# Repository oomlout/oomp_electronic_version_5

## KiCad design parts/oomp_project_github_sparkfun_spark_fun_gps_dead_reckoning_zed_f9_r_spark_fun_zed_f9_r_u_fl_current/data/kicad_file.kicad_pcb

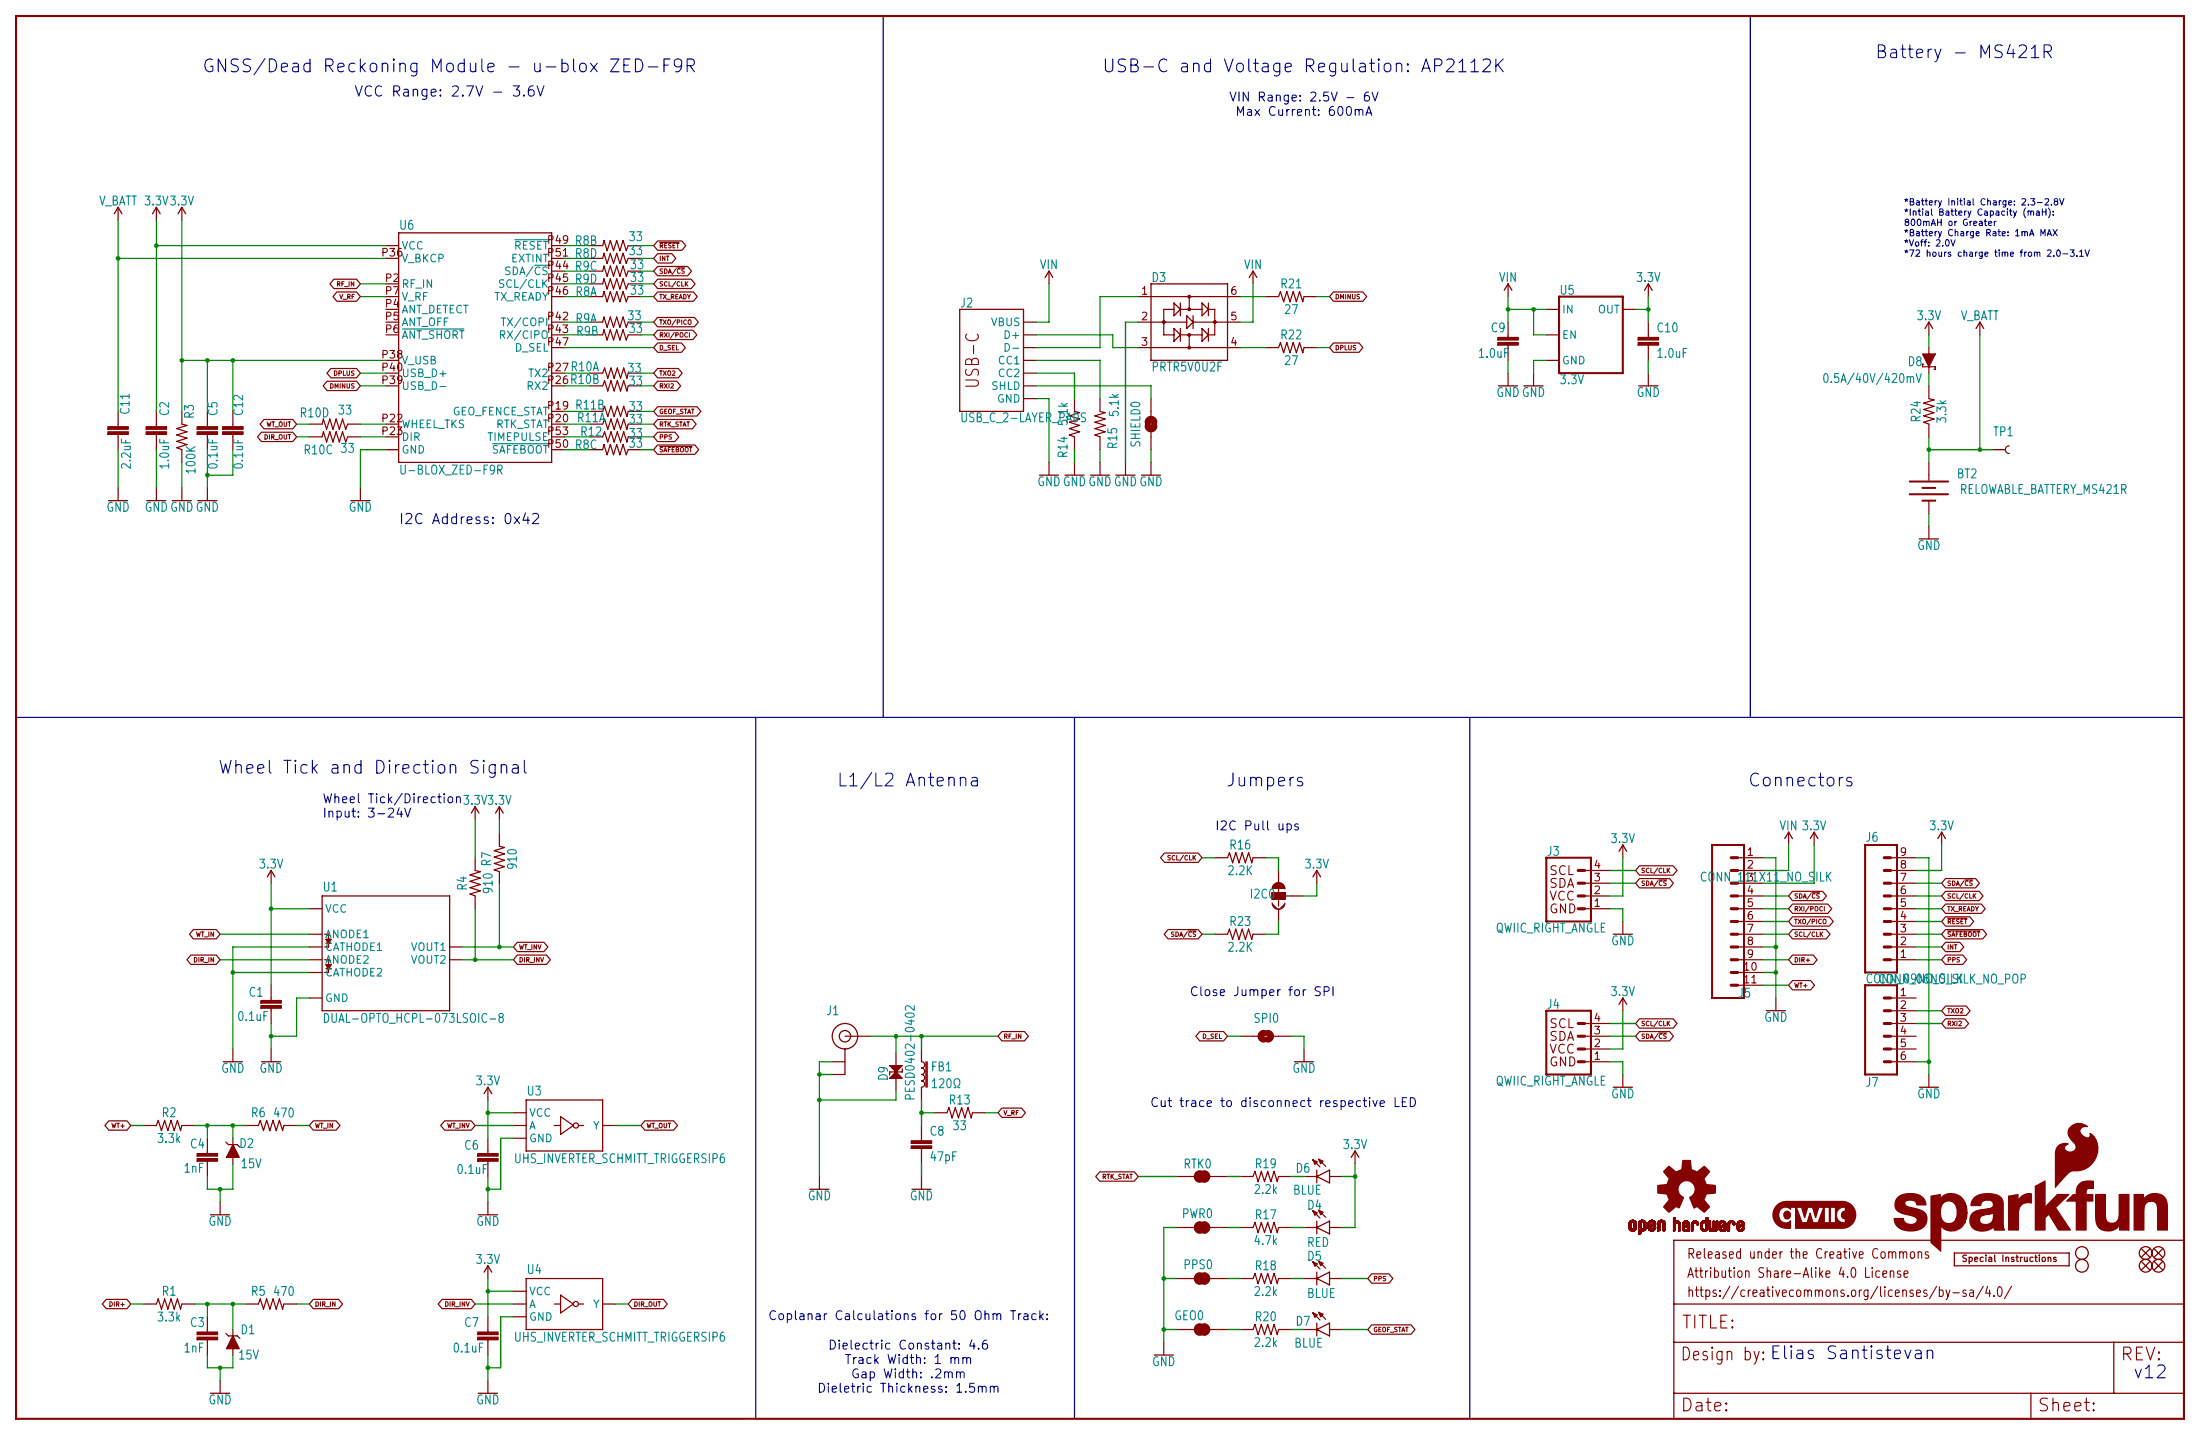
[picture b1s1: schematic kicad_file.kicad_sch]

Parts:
$1_25_$_2020-03-30_22-52-05: STAND-OFFTIGHT; STAND-OFF-TIGHT
BT2: RELOWABLE_BATTERY_MS421R; MS421R_IV03E
C1, C5, C6, C7, C12: 0.1uF; 0402-TIGHT
C2, C9, C10: 1.0uF; 0402-TIGHT
C3, C4: 1nF; 0402
C8: 47pF; 0402
C11: 2.2uF; 0402-TIGHT
D1, D2: 15V; SOT23-3
D3: PRTR5V0U2F; SOT886
D4: RED; LED-0603
D5, D6, D7: BLUE; LED-0603
D8: 0.5A/40V/420mV; SOD-323
D9: PESD0402-0402; 0402; MOUSE_PART 650-PESD0402-140; DIGIKEY_PART PESD0402-140CT-ND
FB1: 120Ω; 0402; MFG_PART BLM15HB121SN1D
FD1, FD2, FD3, FD4: FIDUCIALUFIDUCIAL; FIDUCIAL-MICRO
FRAME1: FRAME-LEDGER; CREATIVE_COMMONS
GEO0: JUMPER-SMT_2_NC_TRACE_SILK; SMT-JUMPER_2_NC_TRACE_SILK
H2: STAND-OFFTIGHT; STAND-OFF-TIGHT
I2C0: JUMPER-SMT_3_2-NC_TRACE_SILK; SMT-JUMPER_3_2-NC_TRACE_SILK
J1: U.FL
J2: USB_C_2-LAYER_PADS; USB-C-16P-2LAYER-PADS
J3, J4: QWIIC_RIGHT_ANGLE; JST04_1MM_RA
J5: CONN_111X11_NO_SILK; 1X11_NO_SILK
J6: CONN_09NO_SILK; 1X09_NO_SILK
J7: CONN_06NO_SILK_NO_POP; 1X06_NO_SILK
LOGO1: OSHW-LOGOS; OSHW-LOGO-S
LOGO2: QWIIC_LOGO_4MM; QWIIC_4MM
LOGO3: SFE_LOGO_NAME_FLAME.2_INCH; SFE_LOGO_NAME_FLAME_.2
LOGO5: SPECIAL_INSTRUCTIONS-ORDERING; ORDERING_INSTRUCTIONS
PPS0: JUMPER-SMT_2_NC_TRACE_SILK; SMT-JUMPER_2_NC_TRACE_SILK
PWR0: JUMPER-SMT_2_NC_TRACE_SILK; SMT-JUMPER_2_NC_TRACE_SILK
R1, R2, R24: 3.3k; 0603
R3: 100K; 0402
R4, R7: 910; 0603
R5, R6: 470; 0603
R8, R9, R10, R11: 33; 1206_RA
R12, R13: 33; 0603
R14, R15: 5.1k; 0402
R16, R23: 2.2K; 0402
R17: 4.7k; 0603
R18, R19, R20: 2.2k; 0603
R21, R22: 27; 0603
RTK0: JUMPER-SMT_2_NC_TRACE_SILK; SMT-JUMPER_2_NC_TRACE_SILK
SHIELD0: JUMPER-SMT_2_NC_TRACE_SILK; SMT-JUMPER_2_NC_TRACE_SILK
SPI0: JUMPER-SMT_2_NO_SILK; SMT-JUMPER_2_NO_SILK
TP1: TEST-POINT3X5; PAD.03X.05
U1: DUAL-OPTO_HCPL-073LSOIC-8; SO08
U3, U4: UHS_INVERTER_SCHMITT_TRIGGERSIP6; SIP6_MICROPAK2
U5: 3.3V; SOT23-5
U6: U-BLOX_ZED-F9R; UBLOX_ZED_F9R

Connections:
3.3V: C1.1, C2.1, C5.1, C6.1, C7.1, C10.1, C12.1, D4.A, D6.A, D8.A, I2C0.2, J3.2, J4.2, J5.3, J6.8, R3.2, R4.2, R7.2, U1.8 (VCC), U3.P6 (VCC), U4.P6 (VCC), U5.5 (OUT), U6.P33 (VCC), U6.P34 (VCC), U6.P38 (V_USB)
DIR+: J5.9, R1.1
DIR_IN: R5.2, U1.4 (ANODE2)
DIR_INV: R4.1, U1.6 (VOUT2), U4.P2 (A)
DIR_OUT: R10.P6 (2), U4.P4 (Y)
DMINUS: R21.2, U6.P39 (USB_D-)
DPLUS: R22.2, U6.P40 (USB_D+)
D_SEL: SPI0.1, U6.P47 (D_SEL)
GEOF_STAT: D7.A, R11.P7 (2)
GND: BT2.-, C1.2, C2.2, C3.2, C4.2, C5.2, C6.2, C7.2, C8.2, C9.2, C10.2, C11.2, C12.2, D1.1 (A), D2.1 (A), D3.2, D9.1, GEO0.1, J1.1 (GND), J1.2 (GND), J2.GND, J2.GND2 (GND), J3.1, J4.1, J5.1, J5.8, J5.10, J6.9, J7.6, PPS0.1, PWR0.1, R3.1, R14.1, R15.1, SHIELD0.1, SPI0.2, U1.2 (CATHODE1), U1.3 (CATHODE2), U1.5 (GND), U3.P3 (GND), U4.P3 (GND), U5.2 (GND), U6.G1 (GND), U6.G2 (GND), U6.G3 (GND), U6.G4 (GND), U6.G5 (GND), U6.G6 (GND), U6.G7 (GND), U6.G8 (GND), U6.G9 (GND), U6.G10 (GND), U6.G11 (GND), U6.G12 (GND), U6.G13 (GND), U6.G14 (GND), U6.G15 (GND), U6.G16 (GND), U6.G17 (GND), U6.G18 (GND), U6.G19 (GND), U6.G20 (GND), U6.G21 (GND), U6.G22 (GND), U6.G23 (GND), U6.G24 (GND), U6.G25 (GND), U6.G26 (GND), U6.G27 (GND), U6.G28 (GND), U6.G29 (GND), U6.G30 (GND), U6.G31 (GND), U6.G32 (GND), U6.G33 (GND), U6.G34 (GND), U6.G35 (GND), U6.G36 (GND), U6.G37 (GND), U6.G38 (GND), U6.G39 (GND), U6.G40 (GND), U6.G41 (GND), U6.G42 (GND), U6.G43 (GND), U6.G44 (GND), U6.G45 (GND), U6.G46 (GND), U6.G47 (GND), U6.G48 (GND), U6.P1 (GND), U6.P3 (GND), U6.P12 (GND), U6.P14 (GND), U6.P32 (GND), U6.P37 (GND), U6.P41 (GND), U6.P48 (GND)
INT: J6.2, R8.P4 (1)
unnamed: I2C0.1, R23.2
unnamed: D8.C, R24.2
unnamed: I2C0.3, R16.2
unnamed: D4.C, R17.2
unnamed: C8.1, FB1.2, R13.1
unnamed: D3.3, J2.A6 (D+), J2.B6 (D+)
unnamed: D3.1, J2.A7 (D-), J2.B7 (D-)
unnamed: PWR0.2, R17.1
unnamed: D3.6, R21.1
unnamed: D3.4, R22.1
unnamed: R8.P7 (2), U6.P49 (~RESET)
unnamed: R8.P5 (2), U6.P51 (EXTINT)
unnamed: J2.B5 (CC2), R14.2
unnamed: J2.A5 (CC1), R15.2
unnamed: R9.P6 (2), U6.P44 (SDA/~CS)
unnamed: R9.P5 (2), U6.P45 (SCL/CLK)
unnamed: R8.P8 (2), U6.P46 (TX_READY)
unnamed: R9.P8 (2), U6.P42 (TX/COPI)
unnamed: R9.P7 (2), U6.P43 (RX/CIPO)
unnamed: R10.P1 (1), U6.P27 (TX2)
unnamed: R19.1, RTK0.2
unnamed: PPS0.2, R18.1
unnamed: D5.C, R18.2
unnamed: D6.C, R19.2
unnamed: R10.P2 (1), U6.P26 (RX2)
unnamed: R11.P2 (1), U6.P19 (GEO_FENCE_STAT)
unnamed: R11.P1 (1), U6.P20 (RTK_STAT)
unnamed: R12.1, U6.P53 (TIMEPULSE)
unnamed: R8.P6 (2), U6.P50 (~SAFEBOOT)
unnamed: R10.P4 (1), U6.P22 (WHEEL_TKS)
unnamed: R10.P3 (1), U6.P23 (DIR)
unnamed: GEO0.2, R20.1
unnamed: D7.C, R20.2
unnamed: C4.1, D2.3 (C), R2.2, R6.1
unnamed: C3.1, D1.3 (C), R1.2, R5.1
PPS: D5.A, J6.1, R12.2
RF_IN: D9.2, FB1.1, J1.FEED (SIGNAL), U6.P2 (RF_IN)
RTK_STAT: R11.P8 (2), RTK0.1
RXI2: J7.3, R10.P7 (2)
RXI/POCI: J5.5, R9.P2 (1)
SCL/CLK: J3.4, J4.4, J5.7, J6.6, R9.P4 (1), R16.1
SDA/~CS: J3.3, J4.3, J5.4, J6.7, R9.P3 (1), R23.1
SHIELD: J2.SHLD1 (SHLD), J2.SHLD2 (SHLD), J2.SHLD3 (SHLD), J2.SHLD4 (SHLD), SHIELD0.2
TXO2: J7.2, R10.P8 (2)
TXO/PICO: J5.6, R9.P1 (1)
TX_READY: J6.5, R8.P1 (1)
VIN: C9.1, D3.5, J2.VBUS1 (VBUS), J2.VBUS2 (VBUS), J5.2, U5.1 (IN), U5.3 (EN)
V_BATT: BT2.+, C11.1, R24.1, TP1.1, U6.P36 (V_BKCP)
V_RF: R13.2, U6.P7 (V_RF)
WT+: J5.11, R2.1
WT_IN: R6.2, U1.1 (ANODE1)
WT_INV: R7.1, U1.7 (VOUT1), U3.P2 (A)
WT_OUT: R10.P5 (2), U3.P4 (Y)
~RESET: J6.4, R8.P2 (1)
~SAFEBOOT: J6.3, R8.P3 (1)

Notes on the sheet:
L1/L2 Antenna
Jumpers
Wheel Tick and Direction Signal
USB-C and Voltage Regulation: AP2112K
Close Jumper for SPI
Cut trace to disconnect respective LED
GNSS/Dead Reckoning Module - u-blox ZED-F9R
I2C Address: 0x42
Elias Santistevan
Connectors
Wheel Tick/Direction Input: 3-24V
VIN Range: 2.5V - 6V Max Current: 600mA
Coplanar Calculations for 50 Ohm Track:
VCC Range: 2.7V - 3.6V
Battery - MS421R
I2C Pull ups
Dielectric Constant: 4.6 Track Width: 1 mm Gap Width: .2mm Dieletric Thickness: 1.5mm
*Battery Initial Charge: 2.3-2.8V *Intial Battery Capacity (maH): 800mAH or Greater *Battery Charge Rate: 1mA MAX *Voff: 2.0V *72 hours charge time from 2.0-3.1V
v12

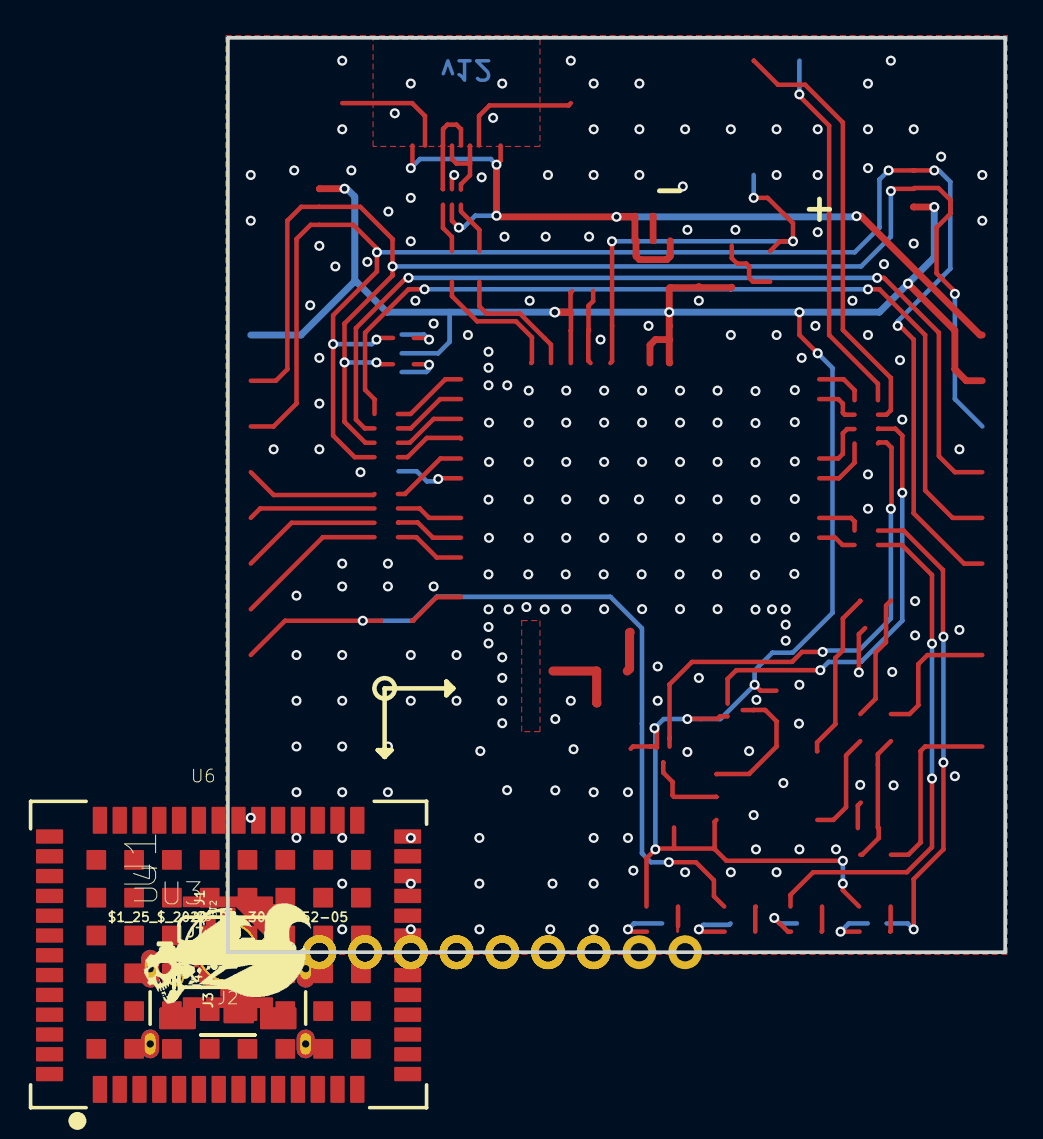
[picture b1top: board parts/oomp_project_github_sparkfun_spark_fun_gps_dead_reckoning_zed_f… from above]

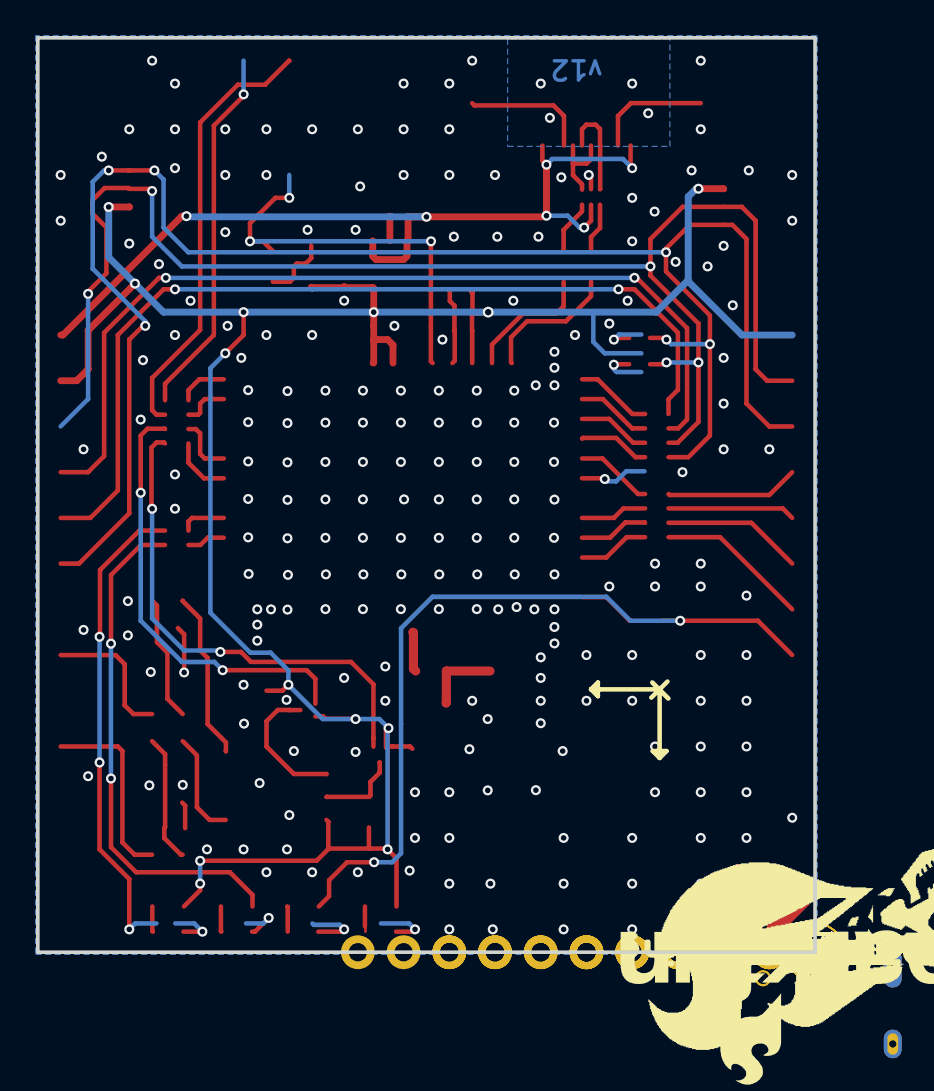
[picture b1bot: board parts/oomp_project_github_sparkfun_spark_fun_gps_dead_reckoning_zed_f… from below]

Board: 2 copper layers, 43.2 x 50.8 mm, 155 parts (50 on the bottom side), 66 nets.

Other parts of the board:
H1, H4: STAND-OFFTIGHT; STAND-OFF-TIGHT
LOGO4: QWIIC_LOGO_4MM; QWIIC_4MM
U$1: ZED#F9R21
U$2: L1#L26
U$3: ANTENNA6
U$4, U$32: X17
U$5, U$6, U$7, U$8, U$9, U$67: #GND#16
U$10: #D##241
U$11: #D##240
U$12: #W##244
U$13: #W##245
U$14, U$15, U$16, U$17: #3V3#17
U$18, U$21: #5V#17
U$19, U$20: DEAD#RECKONING#GPS#BOARD#SILK#FINAL#JPG
U$22: #SDA#235
U$23, U$71: BLK18
U$24: ##CS##25
U$26, U$70: GRN19
U$27: #SDA#236
U$28: #SCL#238
U$29: #TXR#248
U$30: ##RST##28
U$31: ##SFBT##26
U$33: #INT#1
U$34: #INT#0
U$35: #PPS#3
U$37: #SCLK#233
U$38: RXI229
U$39: PWR6
U$40: RTK12
U$41: GEO10
U$42: PPS8
U$43, U$44: Z19
U$45, U$49: Y18
U$46: #SCL#SCLK#2244
U$47: #GEO#12
U$48: #RTK#14
U$50: TXO2234
U$51: #PPS#10
U$52: ##CS##26
U$53: #SPI#4
U$54: #I2C#5
U$57: #SCL#SCLK#2243
U$58: #D##2249
U$59: #D##2248
U$60: #W##2253
U$61: #W##2252
U$62: #TXR#2255
U$63: ##RST##27
U$64: ##SFBT##29
U$65: #PPS#2
U$66: #PWR#8
U$68: #RXI2#34
U$69: #TXO2#235
U$72: GPS_DEAD_RECKONING24
U$73: ZED#F9R25
U$74: #SHLD#2258
U$75: #PICO#2
U$76: #POCI#3
U$77: #RXI#POCI#15
U$78: #TXO#PICO#16

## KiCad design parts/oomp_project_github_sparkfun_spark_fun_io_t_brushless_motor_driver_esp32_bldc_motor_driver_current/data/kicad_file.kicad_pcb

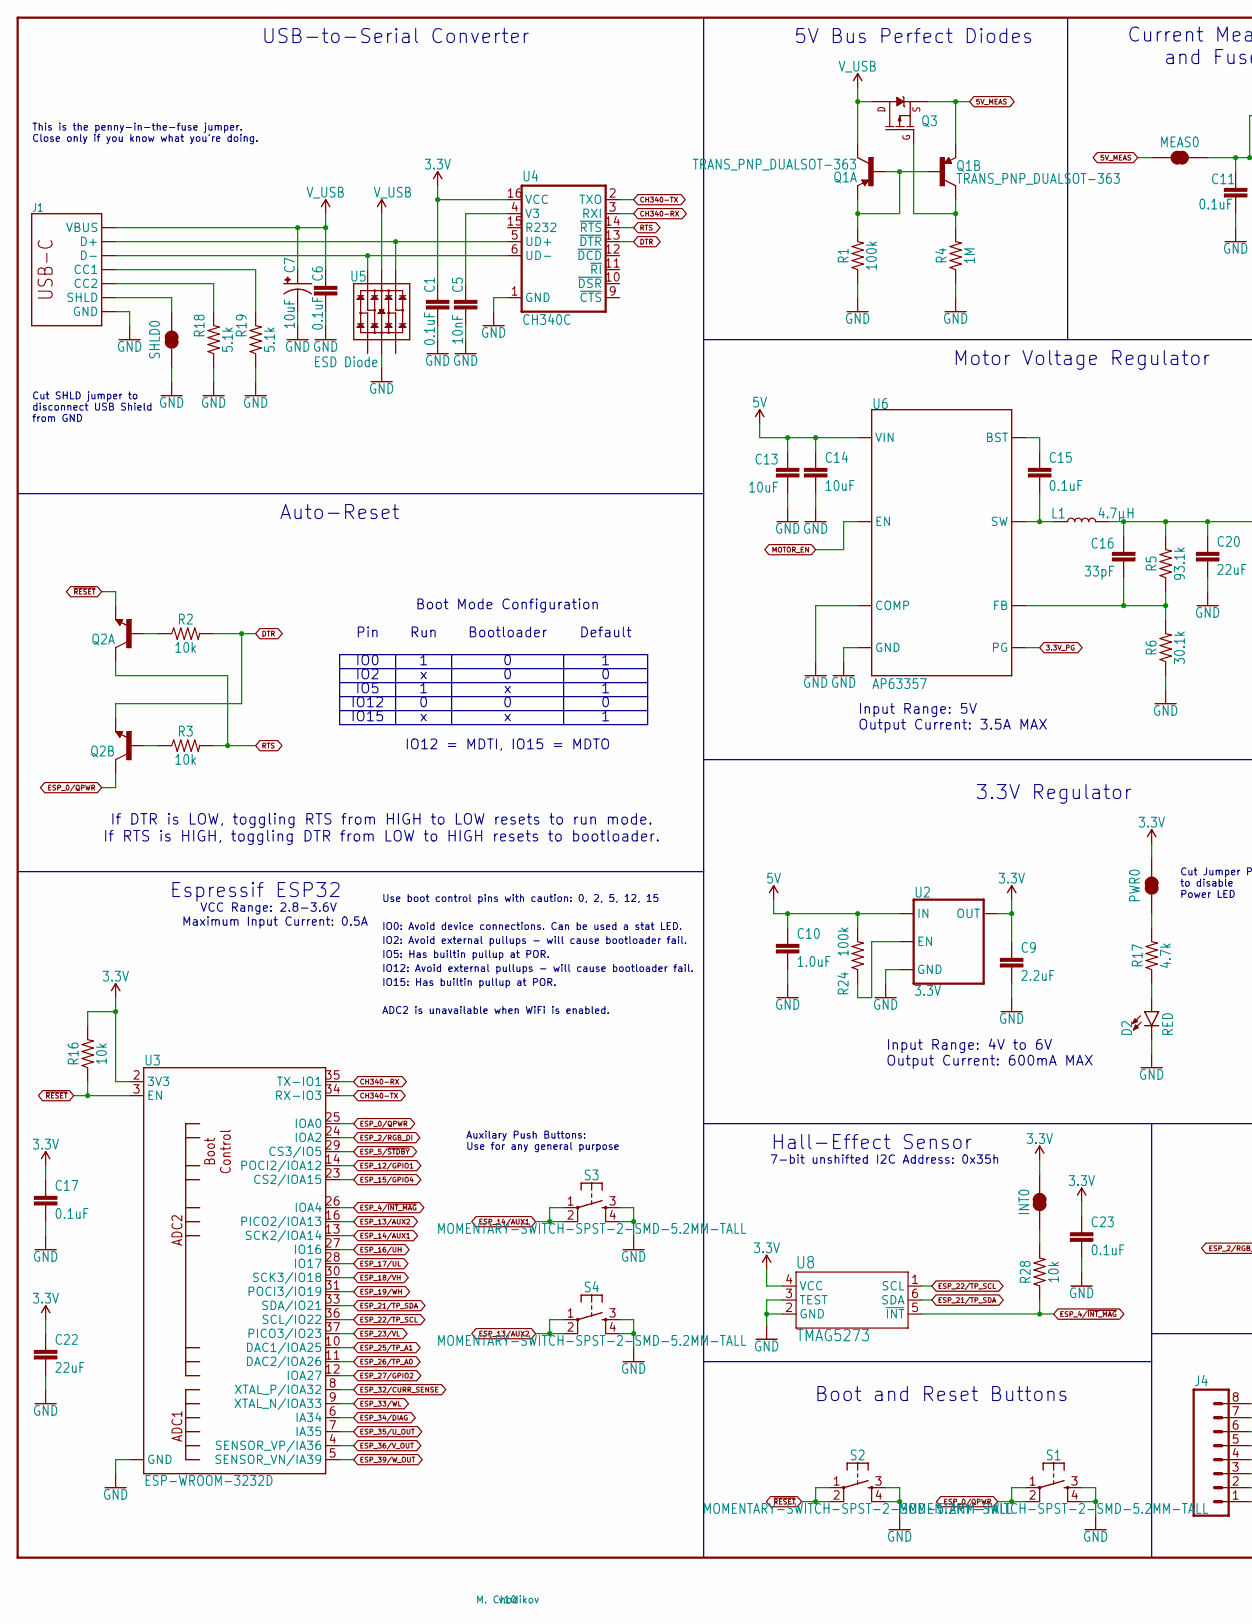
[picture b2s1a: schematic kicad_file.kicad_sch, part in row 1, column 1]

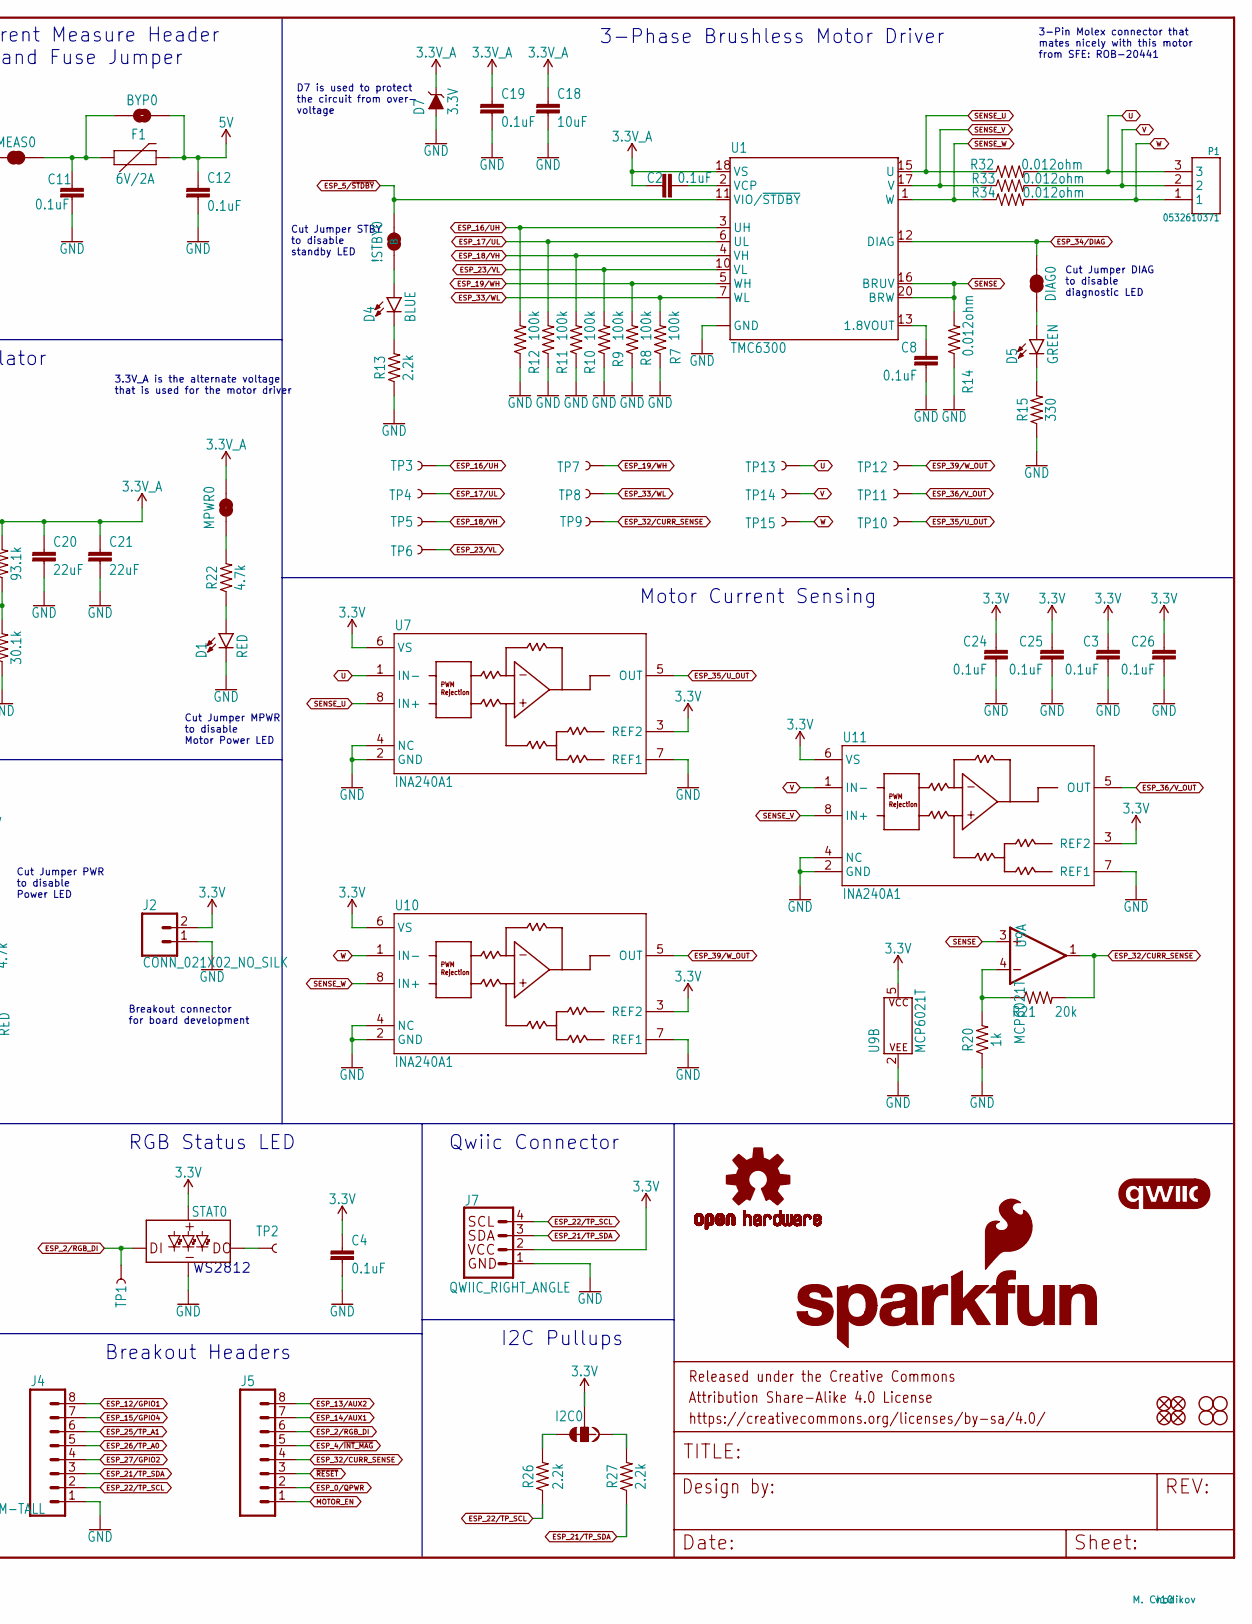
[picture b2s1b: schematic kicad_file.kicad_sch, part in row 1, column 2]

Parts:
!STBY0: JUMPER-SMT_2_NC_TRACE_SILK; SMT-JUMPER_2_NC_TRACE_SILK
BYP0: JUMPER-SMT_2_NO_SILK; SMT-JUMPER_2_NO_SILK
C1, C2, C3, C4, C6, C8, C11, C12, C15, C17, C19, C24, C25, C26: 0.1uF; 0603
C5: 10nF; 0603
C7: 10uF; 0603-POLAR
C9: 2.2uF; 0603
C10: 1.0uF; 0603
C13, C14, C18: 10uF; 0603
C16: 33pF; 0603
C20, C21, C22: 22uF; 0603
C23: 0.1uF; 0402
D1, D2: RED; LED-0603
D4: BLUE; LED-0603
D5: GREEN; LED-0603
D7: 3.3V; SOD-323
DIAG0: JUMPER-SMT_2_NC_TRACE_SILK; SMT-JUMPER_2_NC_TRACE_SILK
F1: 6V/2A; 1210
FD1, FD2, FD3, FD4: FIDUCIALUFIDUCIAL; FIDUCIAL-MICRO
FRAME1: FRAME-LEDGER; CREATIVE_COMMONS
H1, H2, H3, H4: STAND-OFF
I2C0: JUMPER-SMT_3_2-NC_TRACE_SILK; SMT-JUMPER_3_2-NC_TRACE_SILK
INT0: JUMPER-SMT_2_NC_TRACE_SILK; SMT-JUMPER_2_NC_TRACE_SILK
J1: USB-C Connector; USB-C-16P_4LAYER-PADS
J2: CONN_021X02_NO_SILK; 1X02_NO_SILK
J4: Breadboard Connector; 1X08_NO_SILK
J5: Breadboard Headers; 1X08_NO_SILK
J7: QWIIC_RIGHT_ANGLE; JST04_1MM_RA
L1: 4.7μH; INDUCTOR_4X4MM
LOGO1: SFE_LOGO_NAMEBLANK; BLANK
LOGO2: OSHW-LOGOM; OSHW-LOGO-M
LOGO3: SFE_LOGO_FLAME.2_INCH; SFE_LOGO_FLAME_.2
LOGO4: QWIIC_LOGO_5MM; QWIIC_5MM
MEAS0: JUMPER-COMBO_2_NC_TRACE; COMBO-JUMPER_2_NC_TRACE
MPWR0: JUMPER-SMT_2_NC_TRACE_SILK; SMT-JUMPER_2_NC_TRACE_SILK
P1: 0532610371; MOLEX_0532610371
PWR0: JUMPER-SMT_2_NC_TRACE_SILK; SMT-JUMPER_2_NC_TRACE_SILK
Q1: TRANS_PNP_DUALSOT-363; SOT363_PHILIPS
Q2: NPN Transistors; SC70-6
Q3: 20V/4.2A/52mΩ/1.4W; SOT23-3
R1, R7, R8, R9, R10, R11, R12, R24: 100k; 0603
R2, R3, R16, R28: 10k; 0603
R4: 1M; 0603
R5: 93.1k; 0603
R6: 30.1k; 0603
R13, R26, R27: 2.2k; 0603
R14, R32, R33, R34: 0.012ohm; 0603
R15: 330; 0603
R17, R22: 4.7k; 0603
R18, R19: 5.1k; 0603
R20: 1k; 0603
R21: 20k; 0603
S1, S2, S3, S4: MOMENTARY-SWITCH-SPST-2-SMD-5.2MM-TALL; TACTILE_SWITCH_SMD_5.2MM
SHLD0: JUMPER-SMT_2_NC_TRACE_SILK; SMT-JUMPER_2_NC_TRACE_SILK
STAT0: WS2812_2020; WS2812-2020
TP1, TP2, TP3, TP4, TP5, TP6, TP7, TP8, TP9, TP10, TP11, TP12, TP13, TP14, TP15: TEST-POINT3X4; PAD.03X.04
U1: TMC6300; QFN-20
U2: 3.3V; SOT23-5
U3: ESP-WROOM-3232D; ESP-WROOM-32D
U4: CH340C; SO016
U5: ESD Diode; SOT-23-6
U6: AP63357; V-DFN3020-13
U7, U10, U11: INA240A1; D8_TEX
U8: TMAG5273; SOT23-6_DBV_TEX
U9: MCP6021T; SOT23-5

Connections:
1.8_VOUT: C8.1, U1.13 (1.8VOUT)
3.3V: C1.1, C3.1, C4.1, C9.1, C17.1, C22.1, C23.1, C24.1, C25.1, C26.1, I2C0.2, INT0.2, J2.2, J7.2, PWR0.2, R16.2, STAT0.VCC, U2.5 (OUT), U3.2 (3V3), U4.16 (VCC), U7.3 (REF2), U7.6 (VS), U8.4 (VCC), U9.5 (P$V+), U10.3 (REF2), U10.6 (VS), U11.3 (REF2), U11.6 (VS)
3.3V_A: C2.1, C16.2, C18.1, C19.1, C20.1, C21.1, D7.C, L1.P$2 (2), MPWR0.2, R5.2, U1.18 (VS)
3.3V_PG: U6.P$5 (PG)
5V: BYP0.2, C10.1, C12.1, C13.1, C14.1, F1.2, R24.2, U2.1 (IN), U6.P$1 (VIN)
5V_MEAS: MEAS0.1, MEAS0.3 (1), Q1.4 (E), Q3.2 (S)
BST: C15.1, U6.P$6 (BST)
CH340-RX: U3.35 (TX-IO1), U4.3 (RXI)
CH340-TX: U3.34 (RX-IO3), U4.2 (TXO)
D: D5.A, DIAG0.1
D+: J1.A6 (D+), J1.B6 (D+), U4.5 (UD+), U5.4 (IO3)
D-: J1.A7 (D-), J1.B7 (D-), U4.6 (UD-), U5.6 (IO4)
DTR: Q2.1 (E), R2.2, U4.13 (~DTR)
ESP_0/QPWR: J5.2, Q2.6 (C), S1.1, S1.2, U3.25 (IOA0)
ESP_2/RGB_DI: J5.6, STAT0.DI, TP1.1, U3.24 (IOA2)
ESP_4/~INT_MAG: J5.5, R28.1, U3.26 (IOA4), U8.5 (~INT)
ESP_5/~STDBY: !STBY0.2, U1.11 (VIO/~STDBY), U3.29 (CS3/IO5)
ESP_12/GPIO1: J4.8, U3.14 (POCI2/IOA12)
ESP_13/AUX2: J5.8, S4.1, S4.2, U3.16 (PICO2/IOA13)
ESP_14/AUX1: J5.7, S3.1, S3.2, U3.13 (SCK2/IOA14)
ESP_15/GPIO4: J4.7, U3.23 (CS2/IOA15)
ESP_16/UH: R12.2, TP3.1, U1.3 (UH), U3.27 (IO16)
ESP_17/UL: R11.2, TP4.1, U1.6 (UL), U3.28 (IO17)
ESP_18/VH: R10.2, TP5.1, U1.4 (VH), U3.30 (SCK3/IO18)
ESP_19/WH: R8.2, TP7.1, U1.5 (WH), U3.31 (POCI3/IO19)
ESP_21/TP_SDA: J4.3, J7.3, R27.1, U3.33 (SDA/IO21), U8.6 (SDA)
ESP_22/TP_SCL: J4.2, J7.4, R26.1, U3.36 (SCL/IO22), U8.1 (SCL)
ESP_23/VL: R9.2, TP6.1, U1.10 (VL), U3.37 (PICO3/IO23)
ESP_25/TP_A1: J4.6, U3.10 (DAC1/IOA25)
ESP_26/TP_A0: J4.5, U3.11 (DAC2/IOA26)
ESP_27/GPIO2: J4.4, U3.12 (IOA27)
ESP_32/CURR_SENSE: J5.4, R21.2, TP9.1, U3.8 (XTAL_P/IOA32), U9.1 (OUT)
ESP_33/WL: R7.2, TP8.1, U1.7 (WL), U3.9 (XTAL_N/IOA33)
ESP_34/DIAG: DIAG0.2, U1.12 (DIAG), U3.6 (IA34)
ESP_35/U_OUT: TP10.1, U3.7 (IA35), U7.5 (OUT)
ESP_36/V_OUT: TP11.1, U3.4 (SENSOR_VP/IA36), U11.5 (OUT)
ESP_39/W_OUT: TP12.1, U3.5 (SENSOR_VN/IA39), U10.5 (OUT)
FB: C16.1, R5.1, R6.2, U6.P$3 (FB)
GND: C1.2, C3.2, C4.2, C5.2, C6.2, C7.-, C8.2, C9.2, C10.2, C11.2, C12.2, C13.2, C14.2, C17.2, C18.2, C19.2, C20.2, C21.2, C22.2, C23.2, C24.2, C25.2, C26.2, D1.C, D2.C, D7.A, J1.GND, J1.GND2 (GND), J2.1, J4.1, J7.1, R1.1, R4.1, R6.1, R7.1, R8.1, R9.1, R10.1, R11.1, R12.1, R13.1, R14.1, R15.1, R18.1, R19.1, R20.1, S1.3, S1.4, S2.3, S2.4, S3.3, S3.4, S4.3, S4.4, SHLD0.1, STAT0.GND, U1.8 (GND), U1.9 (GND), U1.14 (GND), U1.PAD (GND), U2.2 (GND), U3.1 (GND), U3.15 (GND), U3.38 (GND), U3.GND, U3.GNDT1 (GND), U3.GNDT2 (GND), U3.GNDT3 (GND), U3.GNDT4 (GND), U3.GNDT5 (GND), U3.GNDT6 (GND), U3.GNDT7 (GND), U3.GNDT8 (GND), U4.1 (GND), U5.2 (VSS), U6.P$4 (COMP), U6.P$8 (GND), U7.2 (GND), U7.4 (NC), U7.7 (REF1), U8.2 (GND), U8.3 (TEST), U9.2 (P$V-), U10.2 (GND), U10.4 (NC), U10.7 (REF1), U11.2 (GND), U11.4 (NC), U11.7 (REF1)
MOTOR_EN: J5.1, U6.P$2 (EN)
unnamed: J1.A5 (CC1), R19.2
unnamed: C5.1, U4.4 (V3)
unnamed: J1.B5 (CC2), R18.2
unnamed: C2.2, U1.2 (VCP)
unnamed: R24.1, U2.3 (EN)
unnamed: Q2.5 (B), R2.1
unnamed: Q2.2 (B), R3.1
unnamed: D2.A, R17.1
unnamed: INT0.1, R28.2
unnamed: I2C0.3, R26.2
unnamed: I2C0.1, R27.2
unnamed: R20.2, R21.1, U9.4 (-IN)
unnamed: PWR0.1, R17.2
unnamed: BYP0.1, C11.1, F1.1, MEAS0.2, MEAS0.4 (2)
unnamed: Q1.3 (C), Q3.1 (G), R4.2
unnamed: Q1.1 (E), Q1.2 (B), Q1.5 (B), R1.2
unnamed: D1.A, R22.1
unnamed: MPWR0.1, R22.2
unnamed: D4.C, R13.2
unnamed: D5.C, R15.2
RTS: Q2.3 (C), R3.2, U4.14 (~RTS)
S: !STBY0.1, D4.A
SENSE: R14.2, U1.16 (BRUV), U1.20 (BRW), U9.3 (+IN)
SENSE_U: R32.1, U1.15 (U), U7.8 (IN+)
SENSE_V: R33.1, U1.17 (V), U11.8 (IN+)
SENSE_W: R34.1, U1.1 (W), U10.8 (IN+)
SHLD: J1.SHLD1 (SHLD), J1.SHLD2 (SHLD), J1.SHLD3 (SHLD), J1.SHLD4 (SHLD), SHLD0.2
SW: C15.2, L1.P$1 (1), U6.P$7 (SW), U6.P$9 (SW)
TP2: STAT0.DO, TP2.1
U: P1.3, R32.2, TP13.1, U7.1 (IN-)
V: P1.2, R33.2, TP14.1, U11.1 (IN-)
V_USB: C6.1, C7.+, J1.VBUS1 (VBUS), J1.VBUS2 (VBUS), Q1.6 (C), Q3.3 (D), U5.5 (VCC)
W: P1.1, R34.2, TP15.1, U10.1 (IN-)
~RESET: J5.3, Q2.4 (E), R16.1, S2.1, S2.2, U3.3 (EN)

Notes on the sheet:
Breakout Headers
IO12 = MDTI, IO15 = MDTO
Boot and Reset Buttons
Use boot control pins with caution: 0, 2, 5, 12, 15
Auto-Reset
Run
Qwiic Connector
IO2
3-Phase Brushless Motor Driver
Espressif ESP32
VCC Range: 2.8-3.6V
If DTR is LOW, toggling RTS from HIGH to LOW resets to run mode. If RTS is HIGH, toggling DTR from LOW to HIGH resets to bootloader.
ADC2 is unavailable when WiFi is enabled.
3-Pin Molex connector that mates nicely with this motor from SFE: ROB-20441
7-bit unshifted I2C Address: 0x35h
IO12: Avoid external pullups - will cause bootloader fail.
Default
IO0: Avoid device connections. Can be used a stat LED.
IO15: Has builtin pullup at POR.
Cut SHLD jumper to disconnect USB Shield from GND
3.3V Regulator
Motor Current Sensing
This is the penny-in-the-fuse jumper. Close only if you know what you're doing.
Hall-Effect Sensor
Pin
IO5
Cut Jumper MPWR to disable Motor Power LED
IO0
Cut Jumper STBY to disable standby LED
Breakout connector for board development
Input Range: 5V Output Current: 3.5A MAX
Input Range: 4V to 6V Output Current: 600mA MAX
Bootloader
5V Bus Perfect Diodes
Current Measure Header and Fuse Jumper
Auxilary Push Buttons: Use for any general purpose
Boot Mode Configuration
RGB Status LED
IO12
3.3V_A is the alternate voltage that is used for the motor driver

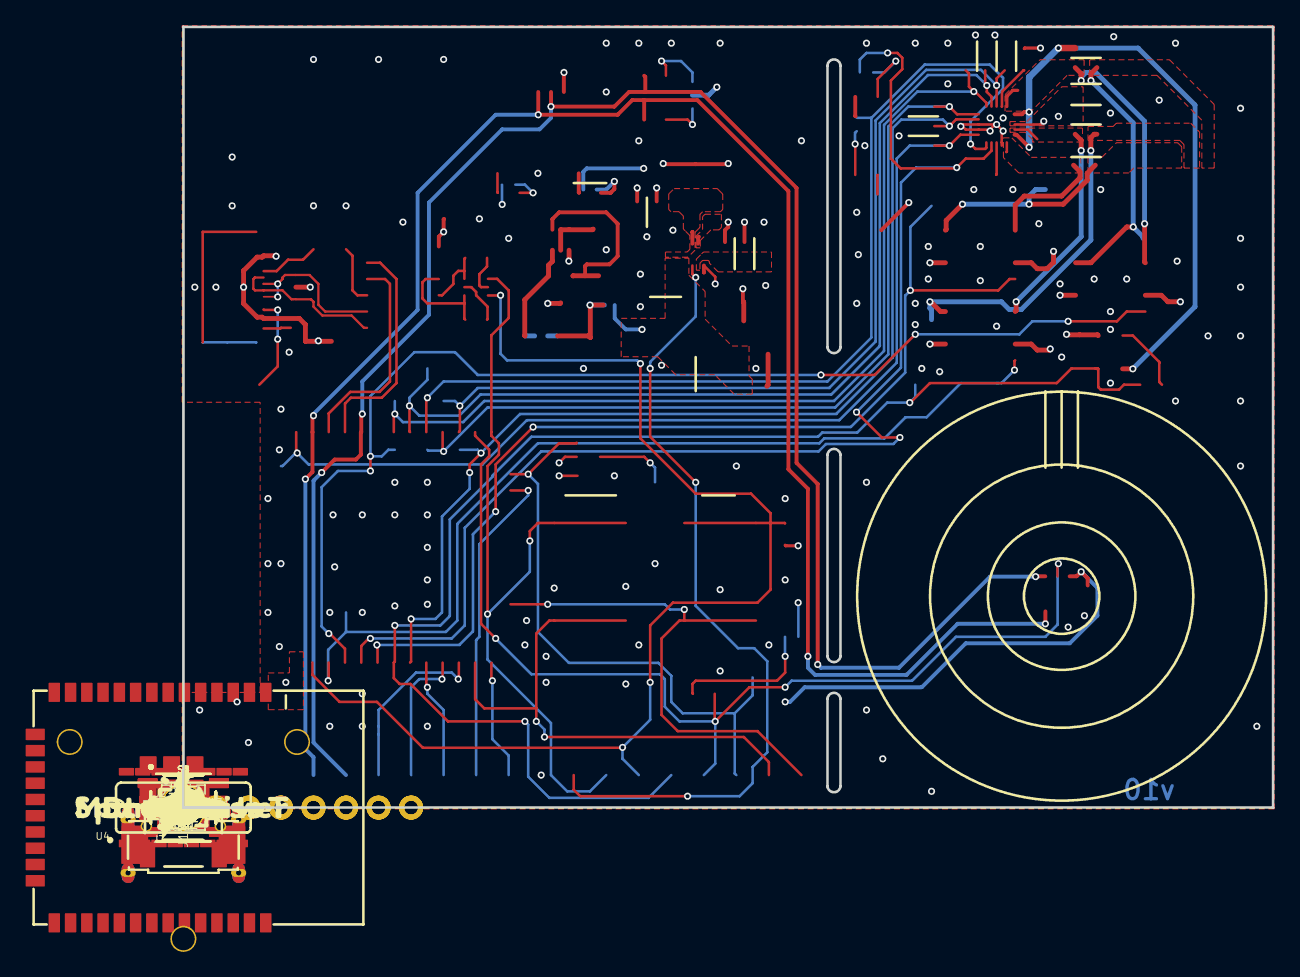
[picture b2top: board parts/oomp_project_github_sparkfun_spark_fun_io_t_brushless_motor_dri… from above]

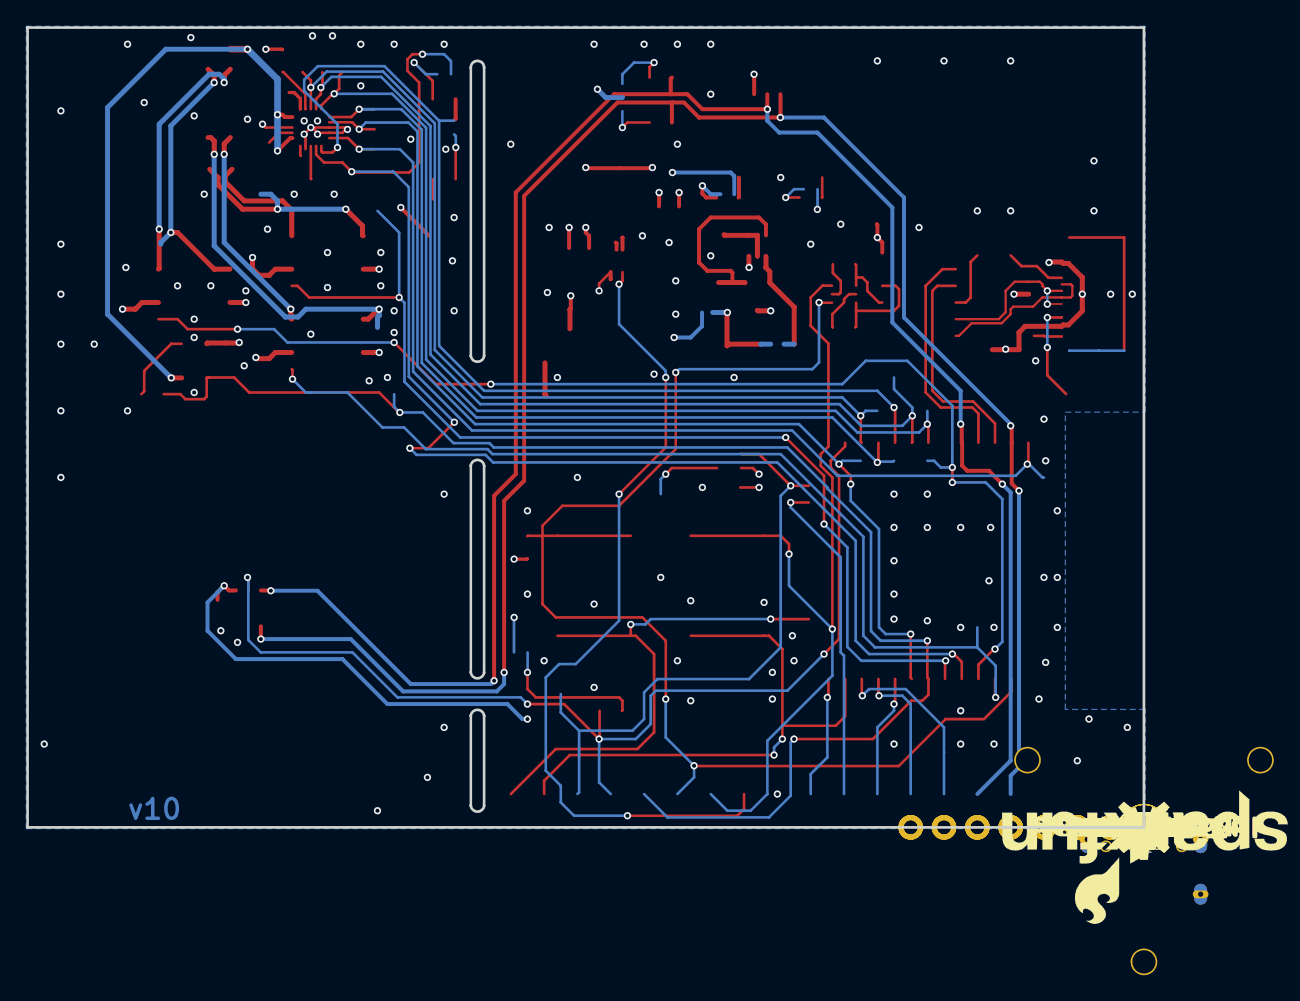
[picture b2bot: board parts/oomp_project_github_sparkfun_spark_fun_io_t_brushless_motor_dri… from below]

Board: 4 copper layers, 85.1 x 61.0 mm, 187 parts (58 on the bottom side), 73 nets.

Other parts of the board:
U$1: ORDERING_INSTRUCTIONS
U$2: OT-EM3215
U$3: 1436
U$4: STAT1630063003522
U$5: RST1630063003525
U$6: #14#AUX1#36
U$7: #12#31
U$8: #DIAG#15
U$9: #14#36
U$10: ##STBY##16
U$11: BOOT21630063003532
U$12: PWR21630063003533
U$13: #MTR_EN#131458
U$14, U$15: #GND#32
U$16, U$58: #3V3#18
U$17: #4#INT_MAG#21630063003534
U$18: #22#33
U$19: #21#33
U$20: #MPWR#131468
U$21: #27#33
U$22: #15#33
U$23: #I2C#630063003467
U$24: #SHLD#630063003467
U$25: ##INT#630063003473
U$26: #32#CURR_SENSE#10
U$27: #PWR#33
U$28, U$60: #GND#17
U$29, U$30: #RESET#34
U$31: #0#33
U$32: #0##BOOT##0
U$33: #32#33
U$34: #4#33
U$35: #12#GPIO1#4
U$36: #2#33
U$37: #15#GPIO4#13
U$38: #13#36
U$39: 131437
U$40: #26#A0#30
U$41: #25#A1#30
U$42: #A1#30
U$43: #BYP#131439
U$44: SPARKFUN_IOT131442
U$45: SFE_LOGO_NAME_FLAME_.2
U$46: BRUSHLESS131445
U$47: MOTOR_DRIVER131446
U$48, U$50: #MEAS#131453
U$49: MPWR131449
U$51: #MTR_EN#131460
U$52: #13#AUX2#14
U$53: #STBY#131470
U$54: #27#GPIO2#27
U$55: IOT_BRUSHLESS131454
U$56: #21#SDA#29
U$57: DIAG131469
U$59: #2#RGB#18
U$62: MOTOR_DRIVER630063003515
U$63: #22#SCL#30
U$64: #A0#30

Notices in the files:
parts/oomp_project_github_sparkfun_spark_fun_gps_dead_reckoning_zed_f9_r_spark_fun_zed_f9_r_u_fl_current/data/kicad_file.kicad_sch:
Released under the Creative Commons
https://creativecommons.org/licenses/by-sa/4.0
parts and their libraries:
Released under the Creative Commons Attribution Share-Alike 4.0 License
